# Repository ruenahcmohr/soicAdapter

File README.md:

# soicAdapter
narrow soic14 to dip adater for breadboarding room.

internet inspired narrow soic14 adapter

5pcs jlcpcb were $4.20 (because I paid with paypal)

The zip file is all the gerber files to have it made.

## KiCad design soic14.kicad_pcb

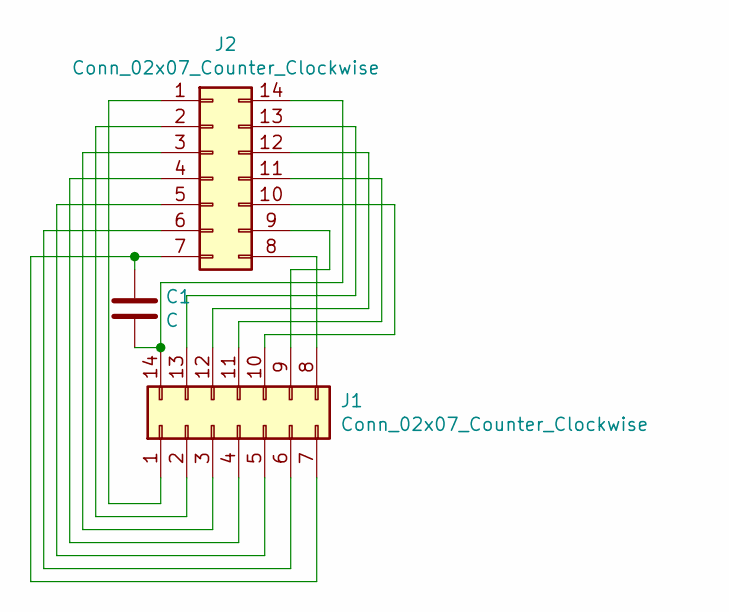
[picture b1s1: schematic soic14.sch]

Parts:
C1: C; C_0805_2012Metric_Pad1.15x1.40mm_HandSolder
J1: Conn_02x07_Counter_Clockwise; DIP-14_W7.62mm_LongPads
J2: Conn_02x07_Counter_Clockwise; SOIC-14_3.9x8.7mm_P1.27mm

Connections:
unnamed: C1.1, J1.7, J2.7
unnamed: C1.2, J1.14, J2.14
unnamed: J1.1, J2.1
unnamed: J1.2, J2.2
unnamed: J1.3, J2.3
unnamed: J1.4, J2.4
unnamed: J1.5, J2.5
unnamed: J1.6, J2.6
unnamed: J1.8, J2.8
unnamed: J1.9, J2.9
unnamed: J1.10, J2.10
unnamed: J1.11, J2.11
unnamed: J1.12, J2.12
unnamed: J1.13, J2.13

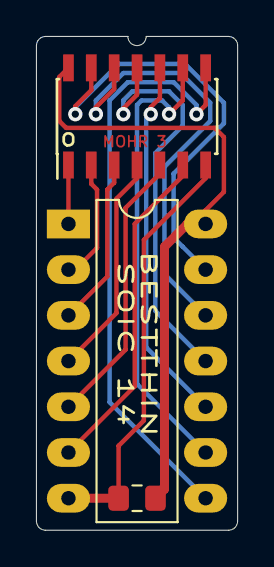
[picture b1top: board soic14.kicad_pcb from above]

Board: 2 copper layers, 11.2 x 27.4 mm, 3 parts (0 on the bottom side), 14 nets.

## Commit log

2025-02-05 adding files
2025-02-05 fixed DRC warning.
2025-02-05 and update images...
2025-02-20 version 3 adds capacitor and combs traces
2025-02-20 oops, cleanout backups
